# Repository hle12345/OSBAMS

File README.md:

# OSBAMS — Rev.2

**OSBAMS Rev.2 is a standalone lithium-ion battery characterization platform optimized
around the SFSU Agilent 6060B electronic load. It uses an STM32L476RG safety controller,
Raspberry Pi 5 interface, INA228-based measurement, independent voltage verification, and
Keysight reference instrumentation to validate capacity, energy, DCIR, thermal behavior, and
battery health metrics of compatible lithium-ion battery packs within the verified hardware envelope.**

Supported: lithium-ion packs, approximately 30–42 V (10S-class; Ninebot/Segway, Shenzhen Elite), XT60 (connector type does not determine test capability — the validated power path does).
Status: **2.0.0-dev1 — host- and simulator-tested; no physical validation has been run**
(nothing is BENCH_TESTED or HARDWARE_VALIDATED).

## The one rule
`allowed current = min(battery profile, OSBAMS hardware limit, 6060B current limit, 300 W / battery voltage)`
at the conservative (never-sagging) pack voltage. 42 V → **7.14 A**; 36 V → **8.33 A**. The 60 A rating never
overrides 300 W. Operating ceiling: ≤ 44 V and ≤ 10 A until the power path is physically validated.

## The Rev.2 stack (`docs/rev2/SFSU_EQUIPMENT_MATRIX.md`)
Agilent/Keysight **6060B** (primary and only external load) · Keysight **EDU34450A** (reference measurement) ·
**Raspberry Pi 5 + 10.1" touchscreen** (UI, database, passport, reports) · **STM32L476RG** (safety controller) ·
**power path** (battery → XT60 → fuse → disconnect → relay → shunt → 6060B) · Keysight **EDUX1052G** (validation-only observation).

## Test orchestrator and dashboard
`services/test_orchestrator.py`: Capacity (`PROFILE → OCV screen → hardware safety check → capability calculation → READY → CC discharge → cutoff → load OFF verified → recovery → results`) and a separate DCIR current-step test. The dashboard shows the live permitted-current breakdown and drives a *manual* 6060B (operator sets/enables the load; OSBAMS verifies from measurements). Hard invariant: commanded current × conservative pack voltage ≤ 300 W; sag never raises current.

## Open at multiple levels
**Current status of the calibration / validation / AI work (under development)**
- The Rev.2 PCB remains frozen at RC1.2e (release candidate, not bench-validated until first article); the validation/AI work makes no PCB or schematic geometry change.
- Protocol v2 firmware is still under development: only a host-side reference parser, golden vectors and design exist; the STM32 firmware still speaks protocol v1.
- Calibration, measurement-quality and agreement thresholds (and the rule-baseline thresholds) are provisional until real bench/reference-instrument measurements exist.
- The AI/data work is experimental/research-stage; no ML-based battery-health result is production-valid yet, and capacity retention vs rated is not a validated cell-level SOH.

OSBAMS is a platform for assessing unknown and second-life batteries, not just a low-cost cycler: **open hardware** (Rev.2 controller PCB review package), **open firmware and software**, **open battery profiles and test protocols**, **open standardized data** (`docs/rev2/DATASET_SCHEMA.md`, Battery Passport) and **open health models** (`ai/`). Chain: Rev.2 hardware → calibration/validation layer → real battery dataset → explainable AI health assessment. The calibration/validation and AI work is **under development**: thresholds are provisional until reference-instrument validation, Rev.2 remains unbench-validated until first article, AI health estimation is experimental/research-stage, and capacity retention is not a validated cell-level SOH. See `docs/rev2/WORKSTREAMS.md`, `docs/rev2/VALIDATION_AND_CALIBRATION_PLAN.md`, `ai/README.md`.

## Hardware workstreams
Two separate hardware workstreams live in this (private) repo: the **Rev.2 controller PCB** (`Hardware/Rev2_Controller/`, RC1.2e) and the **Pi/display power distribution board plus Pi-power interposer** (`OSBAMS_Pi_Display_Power_RevA_RC1/`, `OSBAMS_Pi_Power_Interposer_RevA_RC1/`, generators in `tools/pi_display_power/`; isolated 12 V → 5 V for the Pi 5 + display). Neither is bench-validated. See `docs/rev2/PI_POWER_WORKSTREAM.md`.

## Next milestone: first real battery test
`docs/rev2/FIRST_BATTERY_TEST_PROCEDURE.md`, with `CALIBRATION_RECORD_TEMPLATE.md` and `HARDWARE_ACCEPTANCE_RECORD.md`. Software is ahead of hardware; no more features until measurements exist.

## Bench work
`docs/rev2/BENCH_CHECKLIST.md` — the exact physical tests, in order (workflow: `LV_HARDWARE_VALIDATION_PLAN.md`; verification: `INSTRUMENT_CALIBRATION_PLAN.md`). `docs/rev2/6060B_DRIVER_EVIDENCE.md` — remote-control command evidence (nothing VERIFIED yet).

## Controller PCB manufacturing package
`manufacturing/PCBWay_OSBAMS_Rev2_PCBA/` — candidate Gerber/BOM/CPL/PDFs for the KiCad controller PCB, with a design review and checklist. **Not production-ready** (see its README and checklist).

## Layout
- `desktop/` — Python application (`equipment/`, `services/`, `db/`, `gui/`)
- `Firmware/` — STM32 firmware + host C tests
- `docs/rev2/` — architecture, power-path matrix, current-sensing redesign, GPIB checklist, validation plan, baseline
- `legacy/rev1/` — archived Rev.1 code (nothing may import it)
- `tests/`, `tools/` — Python tests; simulator and demo-data tools

## Run the tests
```
pip install pytest numpy scikit-learn
python3 -m pytest tests          # also: pyserial PySide6 pyqtgraph; QT_QPA_PLATFORM=offscreen
make -C Firmware/Tests run
```
Learning Mode demo: `cd desktop && python3 -m services.learning_mode`.
Simulator: `python3 tools/simulate_serial.py --list`.

## 6060B remote control
`6060B_REMOTE_CONTROL = BLOCKED_BY_INTERFACE_CONFIRMATION` until the lab's GPIB
path is confirmed (`docs/rev2/GPIB_INTERFACE_CONFIRMATION.md`). Use `Manual6060B`
or `Simulator6060B` meanwhile.

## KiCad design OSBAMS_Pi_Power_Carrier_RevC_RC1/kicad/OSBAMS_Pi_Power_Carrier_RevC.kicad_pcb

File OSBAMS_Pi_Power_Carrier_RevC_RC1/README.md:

# OSBAMS_Pi_Power_Carrier_RevC — RC1

**RevC is the size-optimised layout of the combined Pi/display power carrier: same schematic, same parts, same BOM, same 10 mm isolation rule as RevB RC1 (kept unchanged as the previous candidate). Layout-only change, 65 × 50 mm. Modeled quantities are listed in `docs/BENCH_REQUIRED.md` (not verified).** RC2 + interposer remain superseded, reference-only designs.

**Status: review candidate for the owner's local KiCad 10 ERC/DRC and Gerber export. No Gerbers are included; not a fabrication authorization.** `OSBAMS_Pi_Power_Carrier_RevB_RC1` (85 × 67.5 mm) and the RC2 reference design are unchanged.

One board replaces the separate Pi/display power PCB, the Pi interposer and the Micro-Fit harness between them:
`120 VAC → XDR-75-12 → 12 V → J_IN → F1 0407008.WR → TVS1 SMBJ15A → RSDW40F-05 (isolated) → F2 0451008.MRL → 5V_PI → Pi header pins 2,4 (+5 V) / 6,9,14,20 (GND)` and `5V_PI → J_DISP → Waveshare 10.1-DSI-TOUCH-A`.
`PI_GND` is isolated from `12V_GND`; the only link is inside U1.

## Mechanical concept
**65 × 50 mm plain rectangle** (RevB: 85 × 67.5 mm, −43 % area), 2 layers, 1.6 mm, 2 oz Cu. The upper 65 × 42 mm **main body lies entirely outside the Pi 5 outline** (beside/above the Pi's header edge); the lower 8 mm strip is the **plug tab** (Pi y −0.5…7.5 mm) over the header and carries the Samtec SSW-120-01-L-D socket and the header-end spacer holes M1/M2. The RSDW40F-05 lies with its long axis along x (secondary pins at the left, near the Pi's +5 V / GND header pins; primary pins at the right). `J_IN` (top right) faces the top edge, `J_DISP` (bottom left) faces the left edge. The carrier is **not above the CPU / Active Cooler**. Four M3 NPTH holes take **M3 × 20 mm enclosure standoffs**: they carry the carrier's weight (the socket carries none) and K1/K2 double as the **180° key posts** (reversed, they land on bare Pi PCB and stop the socket 2.5 mm short of the pins). `Mechanical_placement_drawing.pdf`, `reports/Mechanical_fit_check.txt`.

## Gates
| Gate | State |
|---|---|
| KiCad 10.0.6 ERC / DRC incl. schematic-parity / unconnected / footprint errors | **0 / 0 / 0 / 0** (`reports/*_kicad10.rpt`); owner re-runs locally |
| Isolation: ≥ 10 mm PRIMARY↔ISOLATED custom rule, negative control, 11 mm copper-free lane, no copper crossing, NPTH holes, no shield | **PASS** (`reports/Isolation_check.txt`, `docs/Isolation_report.md`) |
| Pin map: power only on Pi pins 2, 4 (+5 V) and 6, 9, 14, 20 (GND); 34 pins no-connect; polarity; module pins vs the Mean Well drawing | **PASS** — 97 checks (`reports/Connectivity_pinmap_check.txt`) |
| Mechanical fit (plan view vs Pi 5 drawing, key, heights) | **PASS on paper**; physical fit at first article (no STEP models available) |
| Voltage budget recomputed from scratch | worst case **4.955 V** at the Pi pins with 5 A + 1.0 A display (RevB: 4.962 V, RC2: 4.829 V) — `docs/Voltage_drop_report.md` |
| Bench-required quantities (SSW contact resistance, module joint resistance, real Waveshare current, mechanical fit, reversed-fit key test, no-load maximum 5.234 V) | **BENCH_REQUIRED** — `docs/BENCH_REQUIRED.md` |
| First article | **OPEN (by design)** — `docs/First_article_checklist.md` |
| Gerbers / PCBWay CAM / CPL orientation | **OWNER** |

## Contents
`kicad/` project (`.kicad_pro/.kicad_sch/.kicad_pcb`), libraries `OSBAMS_PiPwr.kicad_sym` + `OSBAMS_PiPwr.pretty`, `fp-lib-table`, `sym-lib-table`, `.kicad_dru` (isolation rule) · `bom/` (incl. mechanical hardware and off-board harness lines) · `cpl/` · `docs/` (this README's references, assembly drawings top/bottom, mechanical placement drawing, voltage-drop report, isolation report, first-article checklist, parts and sources, changes vs RevB, trim calibration, assembly notes) · `reports/`.
Regenerate: `CARRIER_REV=C REL=RC1 python3 tools/pi_display_power/build_carrier_k10.py <out_root>` (needs the `kc10_pi` KiCad 10 container wrapper).

## Open items (none changes the PCB geometry unless noted)
First-article measurements (trim calibration, contact resistances, loaded voltage at the Pi pins and J_DISP, temperatures, Pi + display, throttling, isolation resistance, reversed-fit test); Waveshare maximum current (unpublished); 43030-0038 current rating with 18 AWG; SSW hole 1.0 mm / pad 1.7 mm vs Samtec's recommended hole; Molex 43045 library footprints vs the Molex drawing; manufacturer data that was relayed by the owner (Waveshare, Samtec, SMBJ15A row) is marked user-relayed.

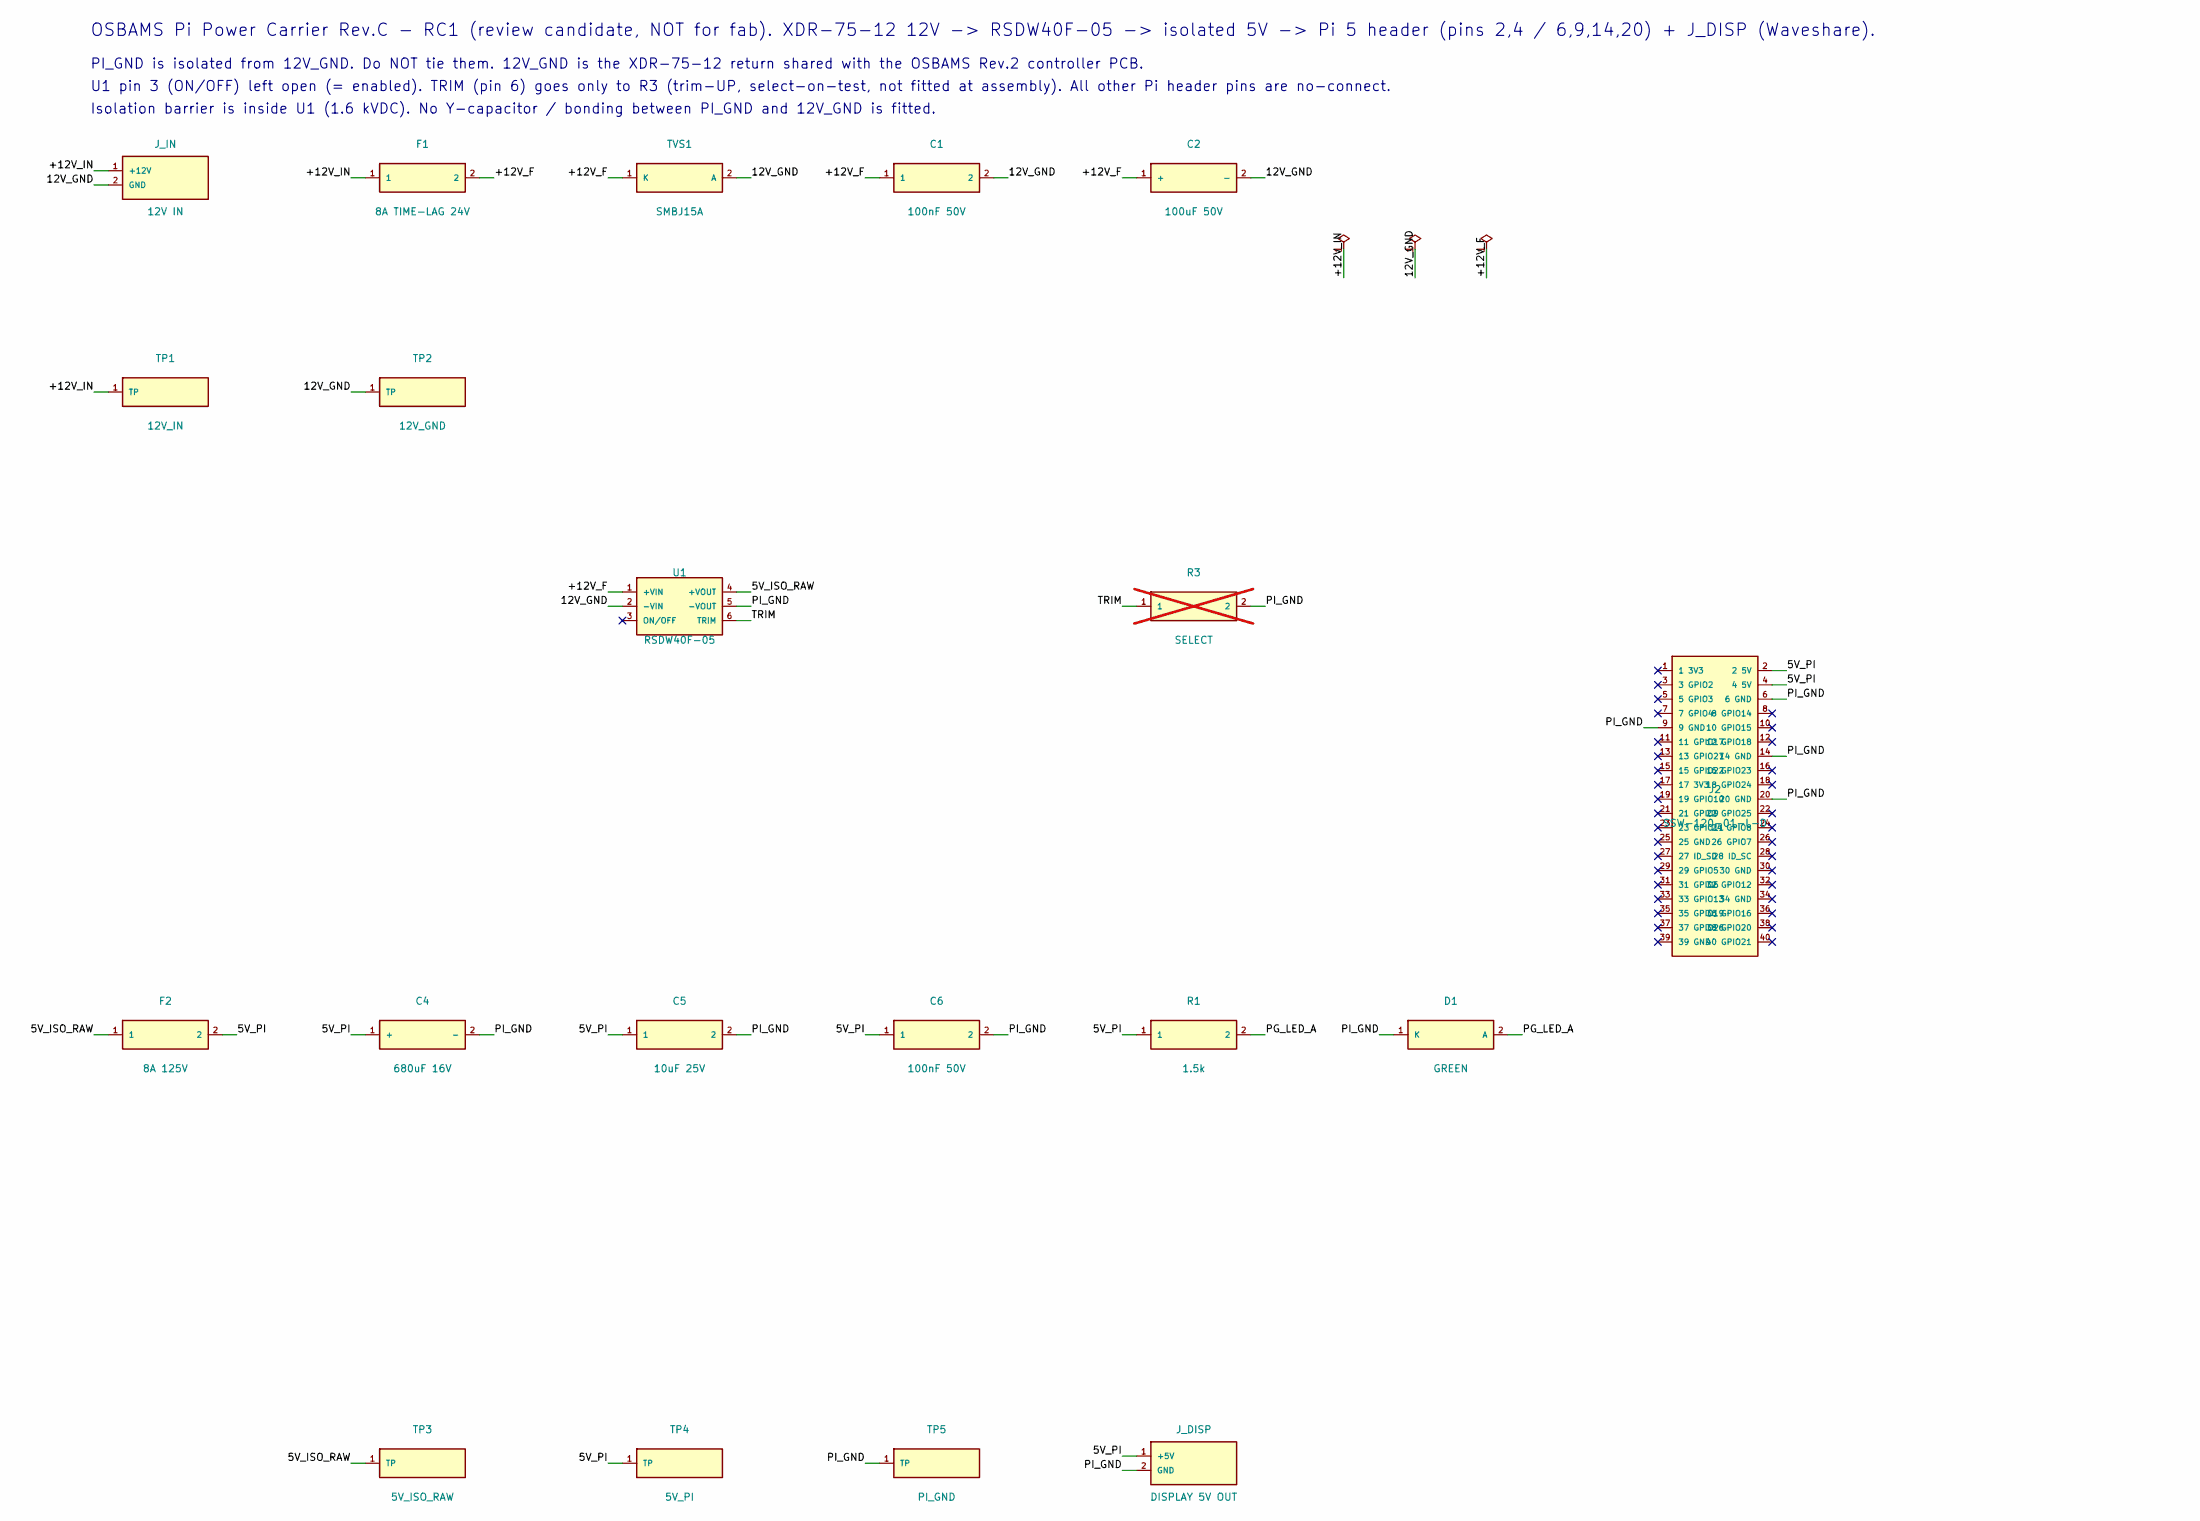
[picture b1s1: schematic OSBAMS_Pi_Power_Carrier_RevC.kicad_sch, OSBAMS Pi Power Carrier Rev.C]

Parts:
C1, C6: 100nF 50V; C_0603_1608Metric; MPN GRM188R71H104KA93D
C2: 100uF 50V; CP_Radial_D8.0mm_P3.50mm; MPN EEU-FM1H101
C4: 680uF 16V; CP_Radial_D10.0mm_P5.00mm; MPN EEU-FR1C681
C5: 10uF 25V; C_0805_2012Metric; MPN GRM21BR61E106KA73L
D1: GREEN; LED_0603_1608Metric; MPN 150060GS75000
F1: 8A TIME-LAG 24V; Fuse_1206_Littelfuse407; MPN 0407008.WR
F2: 8A 125V; Fuse_Littelfuse-NANO2-451_453; MPN 0451008.MRL
J2: SSW-120-01-L-D; SSW-120-01-L-D_RPi_TopView; MPN SSW-120-01-L-D
J_DISP: DISPLAY 5V OUT; Molex_Micro-Fit_3.0_43045-0200_2x01_P3.00mm_Horizontal; MPN 430450200
J_IN: 12V IN; Molex_Micro-Fit_3.0_43045-0200_2x01_P3.00mm_Horizontal; MPN 430450200
R1: 1.5k; R_0603_1608Metric; MPN RC0603FR-071K5L
R3: SELECT; R_0603_1608Metric; MPN RC0603FR-0771K5L (nominal) / -0761K9L /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; not fitted
TP1: 12V_IN; TestPoint_Pad_D1.5mm; MPN 5015
TP2: 12V_GND; TestPoint_Pad_D1.5mm; MPN 5015
TP3: 5V_ISO_RAW; TestPoint_Pad_D1.5mm; MPN 5015
TP4: 5V_PI; TestPoint_Pad_D1.5mm; MPN 5015
TP5: PI_GND; TestPoint_Pad_D1.5mm; MPN 5015
TVS1: SMBJ15A; D_SMB; MPN SMBJ15A
U1: RSDW40F-05; RSDW40F-05_MeanWell_2x1in; MPN RSDW40F-05

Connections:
/5V_ISO_RAW: F2.1, TP3.1, U1.4 (+VOUT)
/5V_PI: C4.1 (+), C5.1, C6.1, F2.2, J2.2 (2 5V), J2.4 (4 5V), J_DISP.1 (+5V), R1.1, TP4.1
/12V_GND: C1.2, C2.2 (-), J_IN.2 (GND), TP2.1, TVS1.2 (A), U1.2 (-VIN)
/+12V_F: C1.1, C2.1 (+), F1.2, TVS1.1 (K), U1.1 (+VIN)
/+12V_IN: F1.1, J_IN.1 (+12V), TP1.1
/PG_LED_A: D1.2 (A), R1.2
/PI_GND: C4.2 (-), C5.2, C6.2, D1.1 (K), J2.6 (6 GND), J2.9 (9 GND), J2.14 (14 GND), J2.20 (20 GND), J_DISP.2 (GND), R3.2, TP5.1, U1.5 (-VOUT)
/TRIM: R3.1, U1.6 (TRIM)

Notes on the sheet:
OSBAMS Pi Power Carrier Rev.C - RC1 (review candidate, NOT for fab). XDR-75-12 12V -> RSDW40F-05 -> isolated 5V -> Pi 5 header (pins 2,4 / 6,9,14,20) + J_DISP (Waveshare).
PI_GND is isolated from 12V_GND. Do NOT tie them. 12V_GND is the XDR-75-12 return shared with the OSBAMS Rev.2 controller PCB.
U1 pin 3 (ON/OFF) left open (= enabled). TRIM (pin 6) goes only to R3 (trim-UP, select-on-test, not fitted at assembly). All other Pi header pins are no-connect.
Isolation barrier is inside U1 (1.6 kVDC). No Y-capacitor / bonding between PI_GND and 12V_GND is fitted.

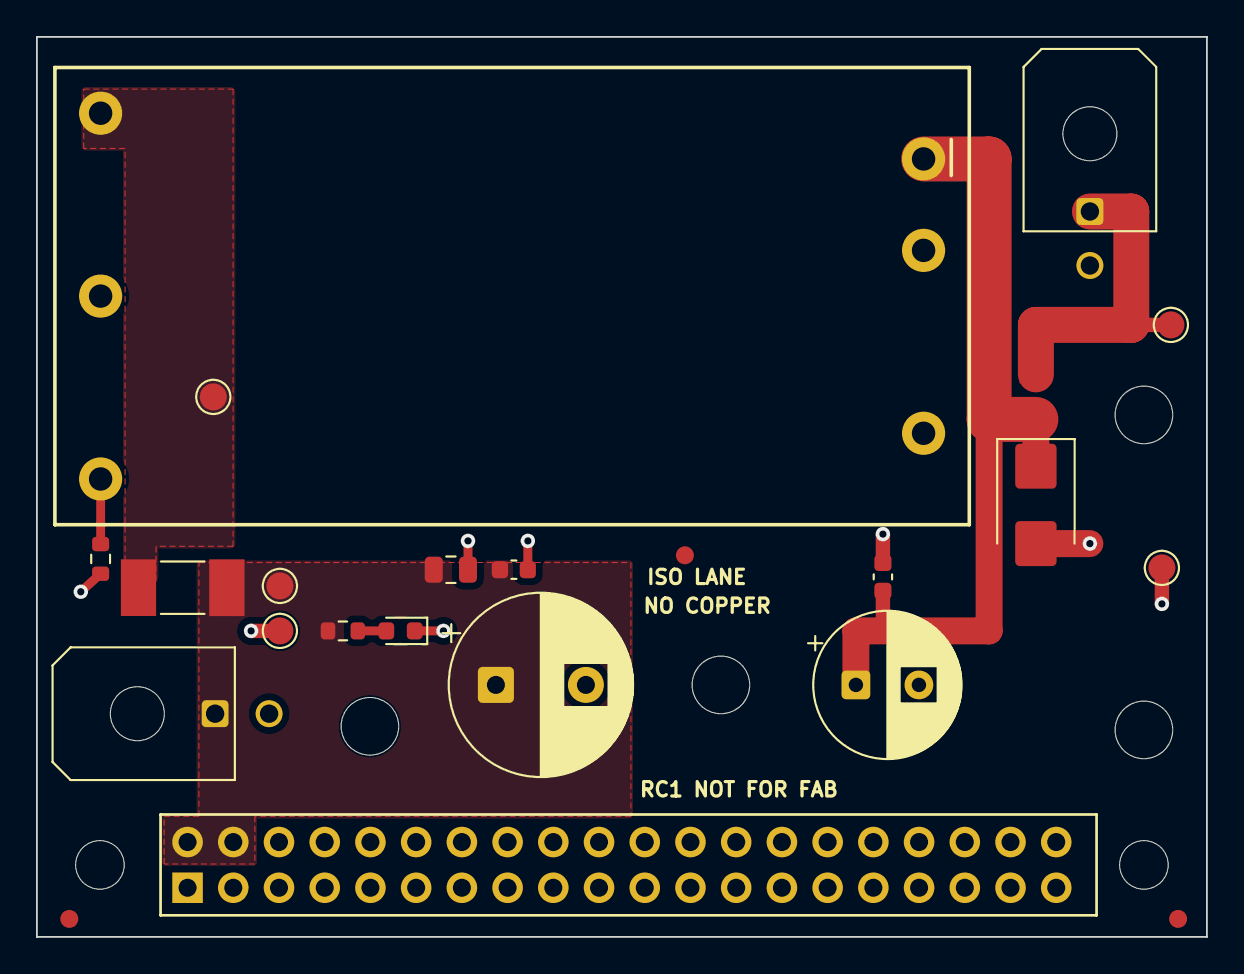
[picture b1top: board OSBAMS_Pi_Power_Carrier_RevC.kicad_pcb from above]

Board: 2 copper layers, 65.0 x 50.0 mm, 29 parts (0 on the bottom side), 8 nets.

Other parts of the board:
FID1, FID2, FID3: Fiducial_1mm_Mask2mm
K1, K2: M3 standoff; MountingHole_3.2mm_M3_Standoff
M1, M2: M2.5 to Pi; MountingHole_2.7mm_M2.5
S3, S4: M3 standoff; MountingHole_3.2mm_M3_Standoff

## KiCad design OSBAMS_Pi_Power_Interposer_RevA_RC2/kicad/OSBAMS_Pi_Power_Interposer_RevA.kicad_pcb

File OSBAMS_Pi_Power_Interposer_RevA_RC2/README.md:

# OSBAMS_Pi_Power_Interposer_RevA — RC2

> **SUPERSEDED / REFERENCE-ONLY by `OSBAMS_Pi_Power_Carrier_RevB_RC1/`** (combined board: worst-case Pi-pin voltage 4.962 V vs 4.829 V here). Kept unchanged as the previous reference design; do not build from it unless RevB is abandoned. PCB geometry is not altered by this note.

Keyed Pi-end interposer for the isolated 5 V supply: Molex Micro-Fit 430450400 (J1) → Samtec **SSW-120-01-L-D** 2 × 20 socket (J2, mounted from the underside) → Raspberry Pi 5 header. **No Gerbers are included; not a fabrication authorization.**

- +5 V on Pi pins **2 and 4**; GND on **6, 9, 14, 20**; the other 34 pins unconnected.
- **Key standoffs K1/K2 (M2.5 × 20 mm) are mandatory**: they prevent the 180° fit that would put +5 V on Pi pin 39 (GND) and GPIO26. Spacers at M1/M2: M2.5 × 11 mm.
- KiCad 10.0.6: ERC 0, DRC 0 (incl. schematic parity), 0 unconnected, 0 footprint errors (`reports/*_kicad10.rpt`).
- Evidence and limits: `docs/Mechanical_verification.md` (Pi 5 drawing, HAT+ geometry, stack height, key), `docs/Keying_analysis.md`, `reports/`.
- Closed: exact socket MPN SSW-120-01-L-D (user-relayed); harness = 18 AWG + Molex 43030-0038 (16 AWG does not fit any 43030 terminal). Open: physical reversed-fit test with a real Pi 5 (first article).
- Project libraries: `kicad/OSBAMS_PiPwr.pretty`, `kicad/OSBAMS_PiPwr.kicad_sym`.

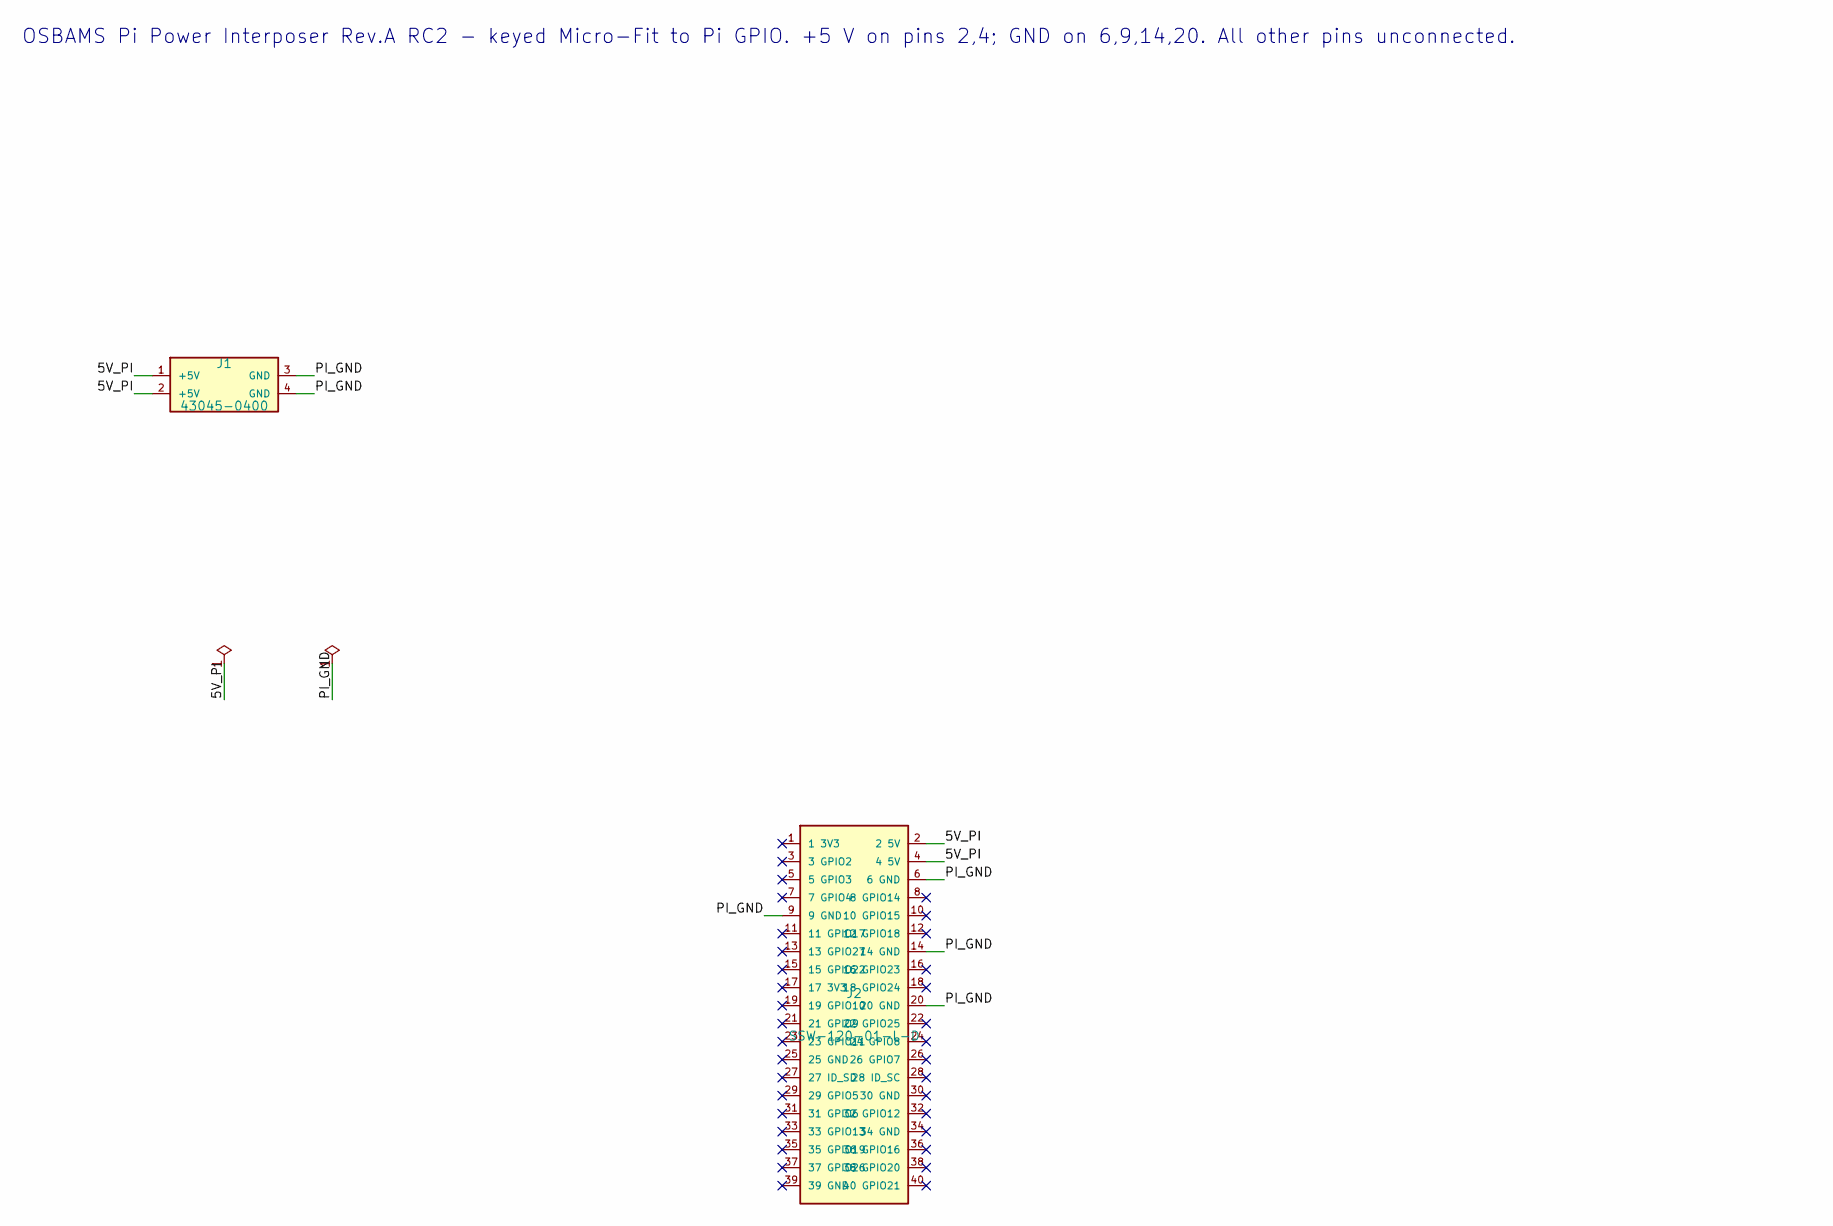
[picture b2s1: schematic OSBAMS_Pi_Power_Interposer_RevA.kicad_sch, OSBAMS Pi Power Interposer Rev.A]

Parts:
J1: 43045-0400; Molex_Micro-Fit_3.0_43045-0400_2x02_P3.00mm_Horizontal; MPN 430450400
J2: SSW-120-01-L-D; SSW-120-01-L-D_RPi_TopView; MPN SSW-120-01-L-D

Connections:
/5V_PI: J1.1 (+5V), J1.2 (+5V), J2.2 (2 5V), J2.4 (4 5V)
/PI_GND: J1.3 (GND), J1.4 (GND), J2.6 (6 GND), J2.9 (9 GND), J2.14 (14 GND), J2.20 (20 GND)

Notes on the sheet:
OSBAMS Pi Power Interposer Rev.A RC2 - keyed Micro-Fit to Pi GPIO. +5 V on pins 2,4; GND on 6,9,14,20. All other pins unconnected.

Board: 2 copper layers, 6 parts (0 on the bottom side), 2 nets, no tracks yet.

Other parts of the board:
K1, K2: KEY M2.5; KeyStandoff_M2.5
M1, M2: M2.5 to Pi; MountingHole_2.7mm_M2.5

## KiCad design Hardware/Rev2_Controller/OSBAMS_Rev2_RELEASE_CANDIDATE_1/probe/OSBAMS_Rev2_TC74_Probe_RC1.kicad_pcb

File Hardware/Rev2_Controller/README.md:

# OSBAMS Rev.2 Controller (new integrated design)

Status: **RELEASE CANDIDATE 1.2 — design package for REVIEW. NOT final, NOT released for fabrication.**
- `OSBAMS_Rev2_RELEASE_CANDIDATE_1/` — KiCad 10 project (schematic, 4-layer PCB, TC74 probe board), BOM/CPL (no Gerbers: export them from the final PCB in KiCad 10), PDFs, ERC/DRC reports, evidence register, supply-chain/DFM/assembly/fab notes, `PCBWAY_RELEASE_CANDIDATE_REPORT.md` (READY FOR REVIEW / BLOCKERS BEFORE PCBWAY ORDER).
- `REV2_CONTROLLER_ARCHITECTURE.md` — architecture (rev D, matches RC1)
- `REV2_CALCULATIONS.md` — generated: `python3 Hardware/Rev2_Controller/calc/rev2_calcs.py` (inputs: `calc/datasheet_inputs.json`, evidence states VERIFIED_LOCAL / USER_RELAYED_MANUFACTURER / UNVERIFIED)
- `REV2_BLOCK_DIAGRAM.png/.svg` (`calc/make_block_diagram.py`), `DATASHEET_VERIFICATION.md` (evidence register)
- `design/` + `build_rc1.py` + `finalize_rc1.py` — generator pipeline (single source of truth `design/rev2_design.py`); `BUILD_ENVIRONMENT.md` explains the KiCad 10 container (`tools/kc10`).
- `reference/` — superseded drafts. Rev.1 KiCad: `legacy/reference/rev1_kicad/` (reference only).
Order: RC1 review → clear every blocker in the RC1 report (manufacturer PDFs, EB21A drawing, local ERC/DRC and Gerber regeneration, stock/lifecycle) → gates in `docs/rev2/pcb/RELEASE_GATES.json` → PCBWay.

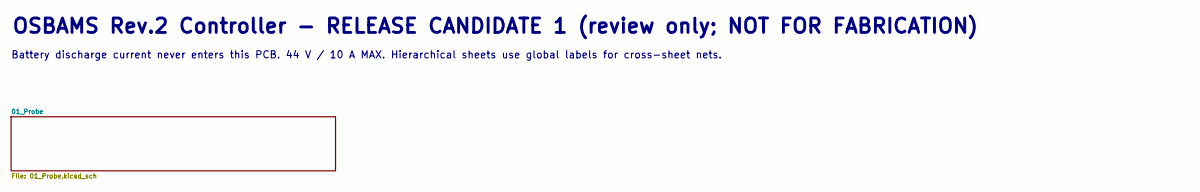
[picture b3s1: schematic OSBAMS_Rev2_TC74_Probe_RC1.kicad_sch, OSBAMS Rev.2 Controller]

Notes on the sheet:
Battery discharge current never enters this PCB. 44 V / 10 A MAX. Hierarchical sheets use global labels for cross-sheet nets.
OSBAMS Rev.2 Controller - RELEASE CANDIDATE 1 (review only; NOT FOR FABRICATION)

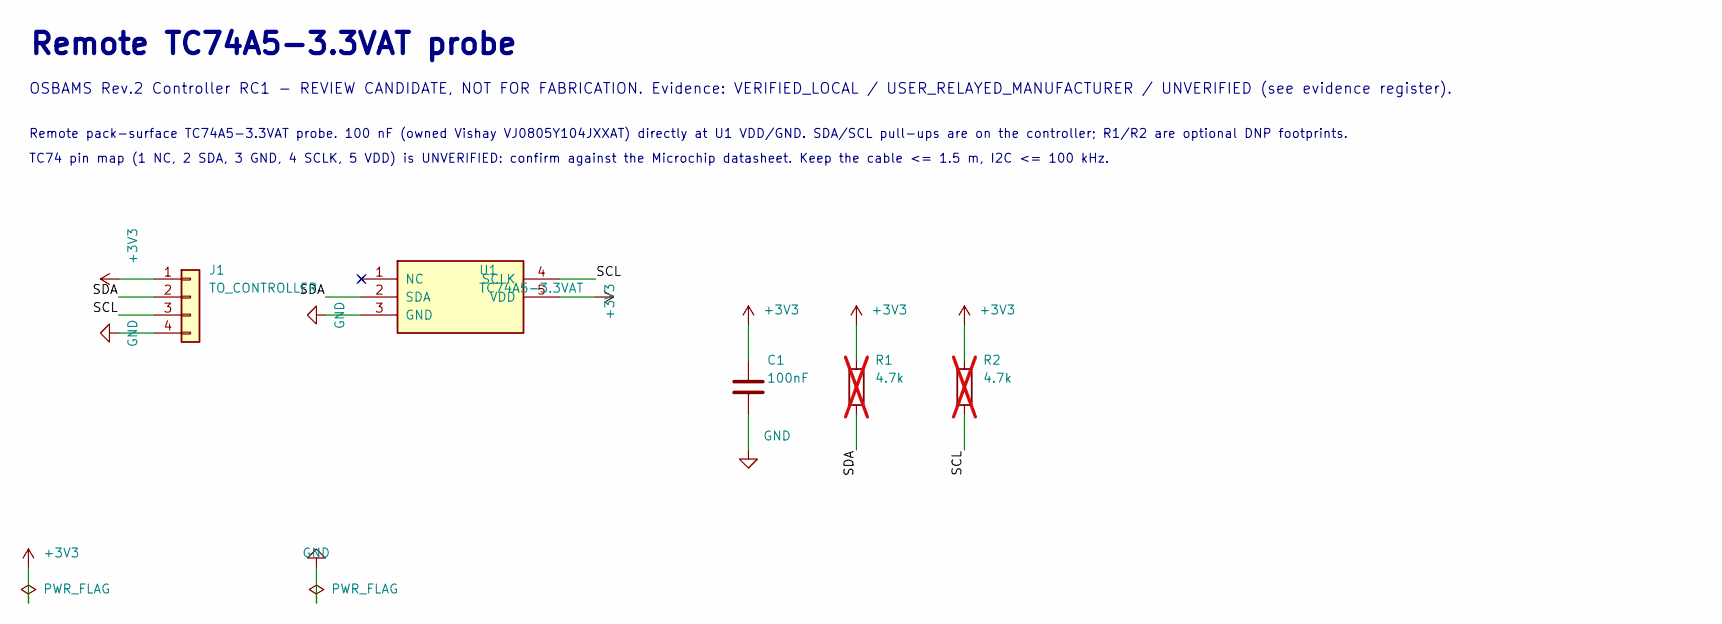
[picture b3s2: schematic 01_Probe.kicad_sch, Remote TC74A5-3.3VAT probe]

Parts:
C1: 100nF; C_0805_2012Metric; MPN VJ0805Y104JXXAT
J1: TO_CONTROLLER; JST_PH_B4B-PH-K_1x04_P2.00mm_Vertical; MPN B4B-PH-K-S
R1, R2: 4.7k; R_0603_1608Metric; MPN CRCW06034K70FKEA; not fitted
U1: TC74A5-3.3VAT; TO-220-5_P3.4x3.7mm_StaggerOdd_Lead3.8mm_Vertical; MPN TC74A5-3.3VAT

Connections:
+3V3: C1.1, J1.1, R1.1, R2.1, U1.5 (VDD)
GND: C1.2, J1.4, U1.3 (GND)
SCL: J1.3, R2.2, U1.4 (SCLK)
SDA: J1.2, R1.2, U1.2 (SDA)

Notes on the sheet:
Remote pack-surface TC74A5-3.3VAT probe. 100 nF (owned Vishay VJ0805Y104JXXAT) directly at U1 VDD/GND. SDA/SCL pull-ups are on the controller; R1/R2 are optional DNP footprints.
TC74 pin map (1 NC, 2 SDA, 3 GND, 4 SCLK, 5 VDD) is UNVERIFIED: confirm against the Microchip datasheet. Keep the cable <= 1.5 m, I2C <= 100 kHz.
OSBAMS Rev.2 Controller RC1 - REVIEW CANDIDATE, NOT FOR FABRICATION. Evidence: VERIFIED_LOCAL / USER_RELAYED_MANUFACTURER / UNVERIFIED (see evidence register).
Remote TC74A5-3.3VAT probe

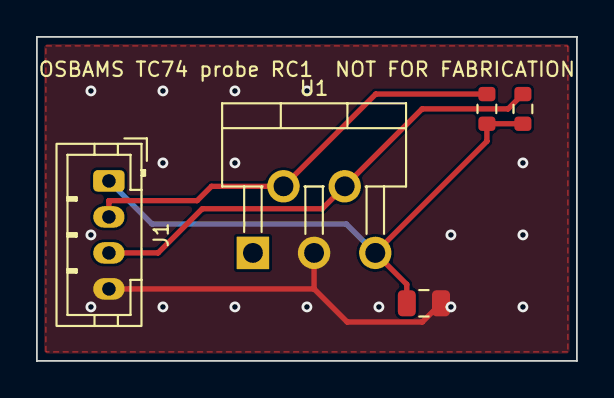
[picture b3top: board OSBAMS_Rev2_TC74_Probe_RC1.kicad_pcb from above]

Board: 2 copper layers, 30.0 x 18.0 mm, 5 parts (0 on the bottom side), 4 nets.

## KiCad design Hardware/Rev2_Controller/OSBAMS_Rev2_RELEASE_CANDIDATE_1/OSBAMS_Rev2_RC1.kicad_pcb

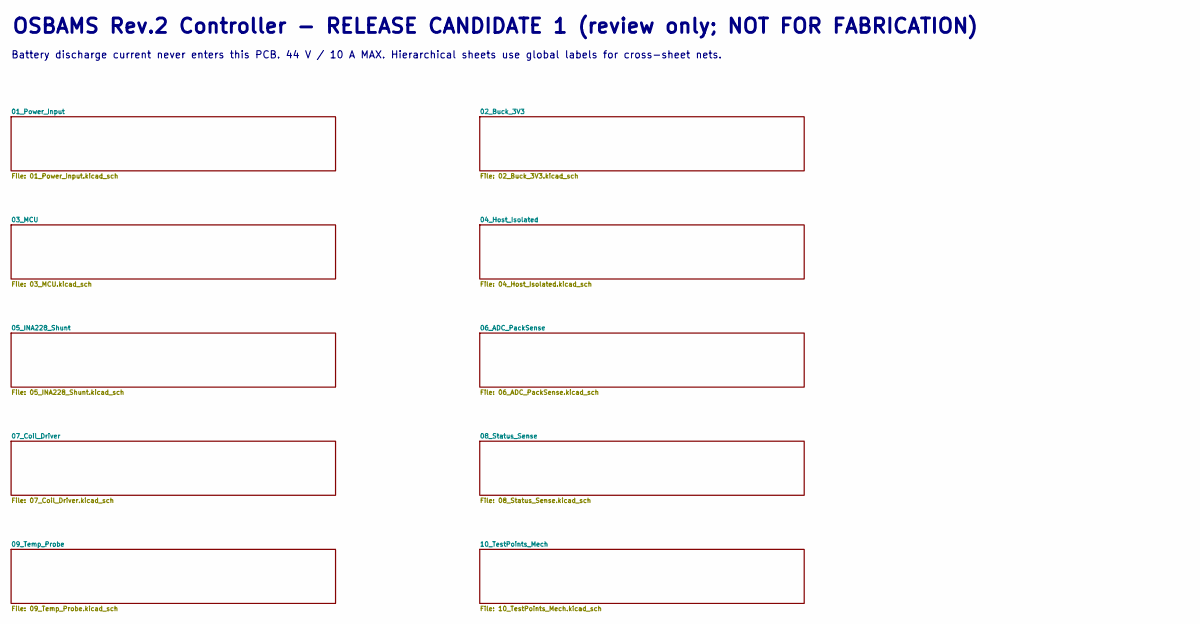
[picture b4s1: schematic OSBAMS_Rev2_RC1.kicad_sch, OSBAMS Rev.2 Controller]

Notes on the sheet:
OSBAMS Rev.2 Controller - RELEASE CANDIDATE 1 (review only; NOT FOR FABRICATION)
Battery discharge current never enters this PCB. 44 V / 10 A MAX. Hierarchical sheets use global labels for cross-sheet nets.

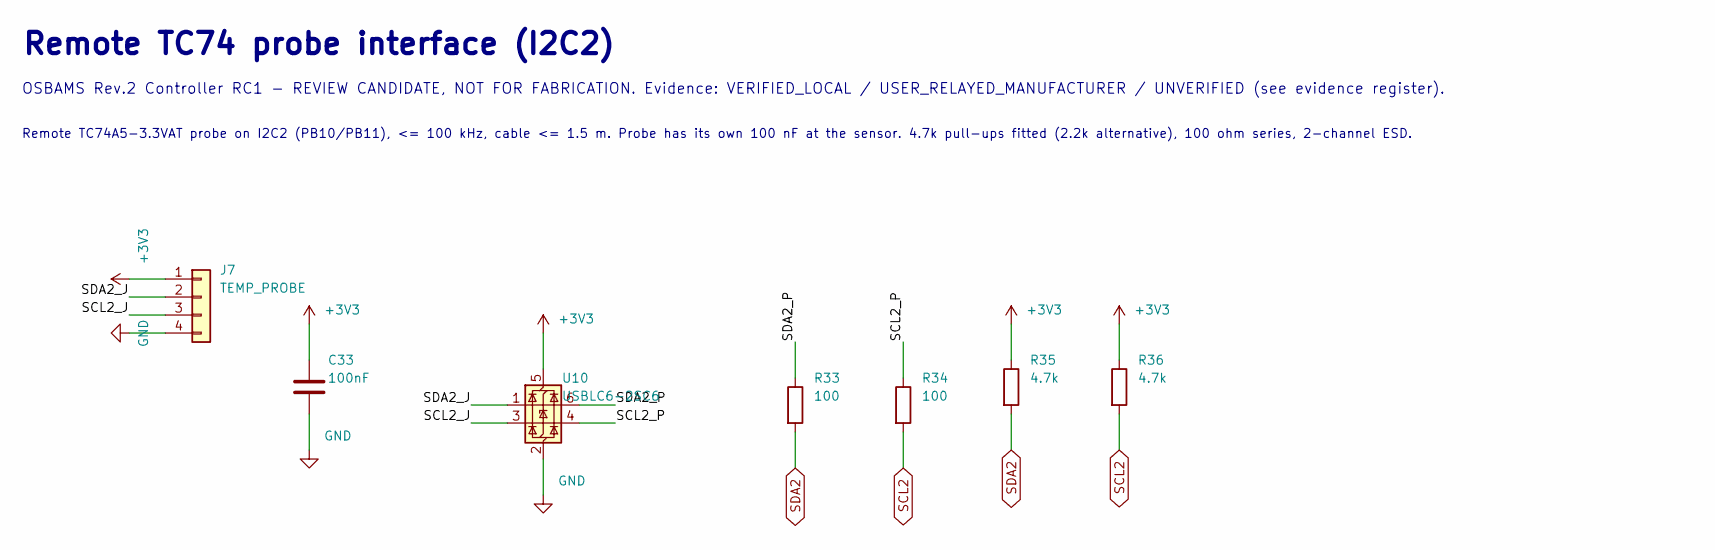
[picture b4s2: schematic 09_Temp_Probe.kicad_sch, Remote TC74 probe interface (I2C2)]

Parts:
C33: 100nF; C_0603_1608Metric; MPN GRM188R71H104KA93D
J7: TEMP_PROBE; JST_PH_B4B-PH-K_1x04_P2.00mm_Vertical; MPN B4B-PH-K-S
R33, R34: 100; R_0603_1608Metric; MPN CRCW0603100RFKEA
R35, R36: 4.7k; R_0603_1608Metric; MPN CRCW06034K70FKEA
U10: USBLC6-2SC6; SOT-23-6; MPN USBLC6-2SC6

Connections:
+3V3: C33.1, J7.1, R35.1, R36.1, U10.5 (VBUS); also elsewhere on the board
/09_Temp_Probe/SCL2_J: J7.3, U10.3 (I/O2)
/09_Temp_Probe/SCL2_P: R34.1, U10.4 (I/O2)
/09_Temp_Probe/SDA2_J: J7.2, U10.1 (I/O1)
/09_Temp_Probe/SDA2_P: R33.1, U10.6 (I/O1)
GND: C33.2, J7.4, U10.2 (GND); also elsewhere on the board
SCL2: R34.2, R36.2; also elsewhere on the board
SDA2: R33.2, R35.2; also elsewhere on the board

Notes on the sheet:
OSBAMS Rev.2 Controller RC1 - REVIEW CANDIDATE, NOT FOR FABRICATION. Evidence: VERIFIED_LOCAL / USER_RELAYED_MANUFACTURER / UNVERIFIED (see evidence register).
Remote TC74 probe interface (I2C2)
Remote TC74A5-3.3VAT probe on I2C2 (PB10/PB11), <= 100 kHz, cable <= 1.5 m. Probe has its own 100 nF at the sensor. 4.7k pull-ups fitted (2.2k alternative), 100 ohm series, 2-channel ESD.

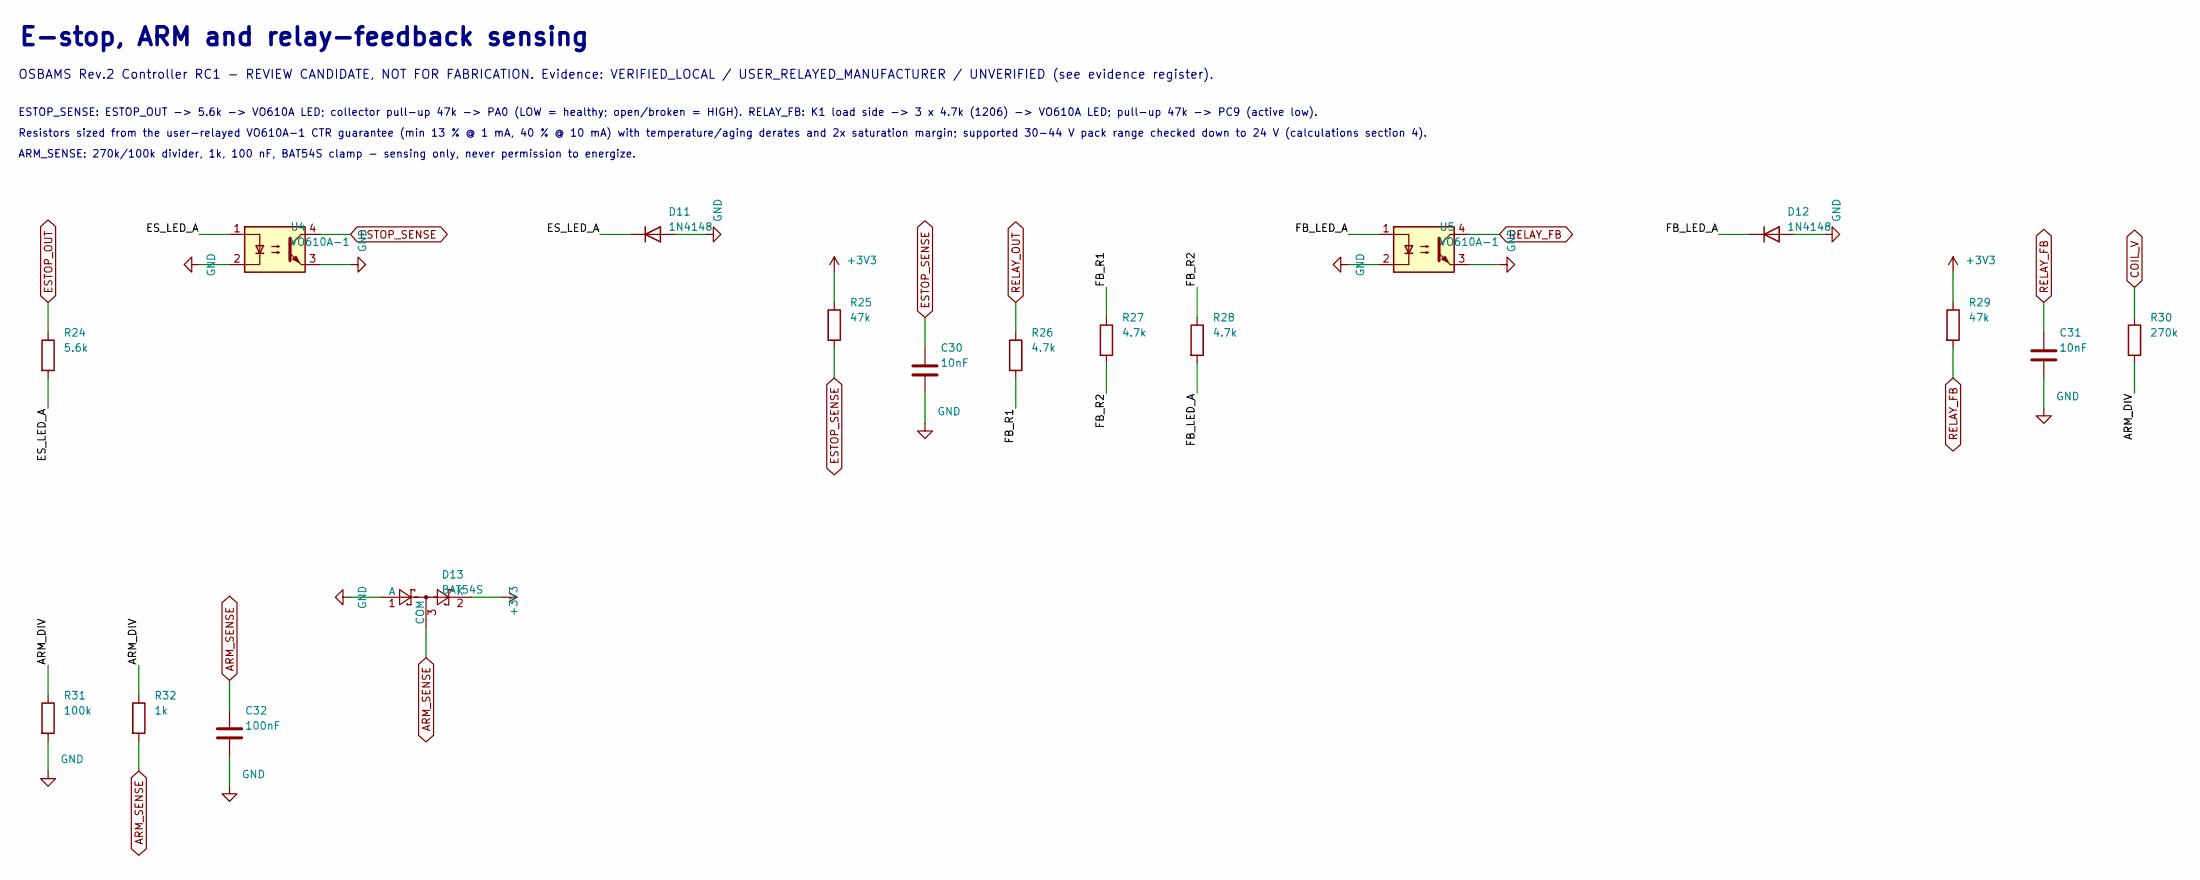
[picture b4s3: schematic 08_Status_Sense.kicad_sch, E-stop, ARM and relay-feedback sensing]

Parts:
C30, C31: 10nF; C_0603_1608Metric; MPN GRM188R71H103KA01D
C32: 100nF; C_0603_1608Metric; MPN GRM188R71H104KA93D
D11, D12: 1N4148; D_DO-35_SOD27_P7.62mm_Horizontal; MPN 1N4148
D13: BAT54S; SOT-23; MPN BAT54S,215
R24: 5.6k; R_0603_1608Metric; MPN CRCW06035K60FKEA
R25, R29: 47k; R_0603_1608Metric; MPN CRCW060347K0FKEA
R26, R27, R28: 4.7k; R_1206_3216Metric; MPN CRCW12064K70FKEA
R30: 270k; R_0603_1608Metric; MPN CRCW0603270KFKEA
R31: 100k; R_0603_1608Metric; MPN CRCW0603100KFKEA
R32: 1k; R_0603_1608Metric; MPN CRCW06031K00FKEA
U4, U5: VO610A-1; DIP-4_W7.62mm; MPN VO610A-1

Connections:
+3V3: D13.2 (K), R25.1, R29.1; also elsewhere on the board
/08_Status_Sense/ARM_DIV: R30.2, R31.1, R32.1
/08_Status_Sense/ES_LED_A: D11.1 (K), R24.2, U4.1
/08_Status_Sense/FB_LED_A: D12.1 (K), R28.2, U5.1
/08_Status_Sense/FB_R1: R26.2, R27.1
/08_Status_Sense/FB_R2: R27.2, R28.1
ARM_SENSE: C32.1, D13.3 (COM), R32.2; also elsewhere on the board
COIL_V: R30.1; also elsewhere on the board
ESTOP_OUT: R24.1; also elsewhere on the board
ESTOP_SENSE: C30.1, R25.2, U4.4; also elsewhere on the board
GND: C30.2, C31.2, C32.2, D11.2 (A), D12.2 (A), D13.1 (A), R31.2, U4.2, U4.3, U5.2, U5.3; also elsewhere on the board
RELAY_FB: C31.1, R29.2, U5.4; also elsewhere on the board
RELAY_OUT: R26.1; also elsewhere on the board

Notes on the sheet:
OSBAMS Rev.2 Controller RC1 - REVIEW CANDIDATE, NOT FOR FABRICATION. Evidence: VERIFIED_LOCAL / USER_RELAYED_MANUFACTURER / UNVERIFIED (see evidence register).
Resistors sized from the user-relayed VO610A-1 CTR guarantee (min 13 % @ 1 mA, 40 % @ 10 mA) with temperature/aging derates and 2x saturation margin; supported 30-44 V pack range checked down to 24 V (calculations section 4).
E-stop, ARM and relay-feedback sensing
ARM_SENSE: 270k/100k divider, 1k, 100 nF, BAT54S clamp - sensing only, never permission to energize.
ESTOP_SENSE: ESTOP_OUT -> 5.6k -> VO610A LED; collector pull-up 47k -> PA0 (LOW = healthy; open/broken = HIGH). RELAY_FB: K1 load side -> 3 x 4.7k (1206) -> VO610A LED; pull-up 47k -> PC9 (active low).

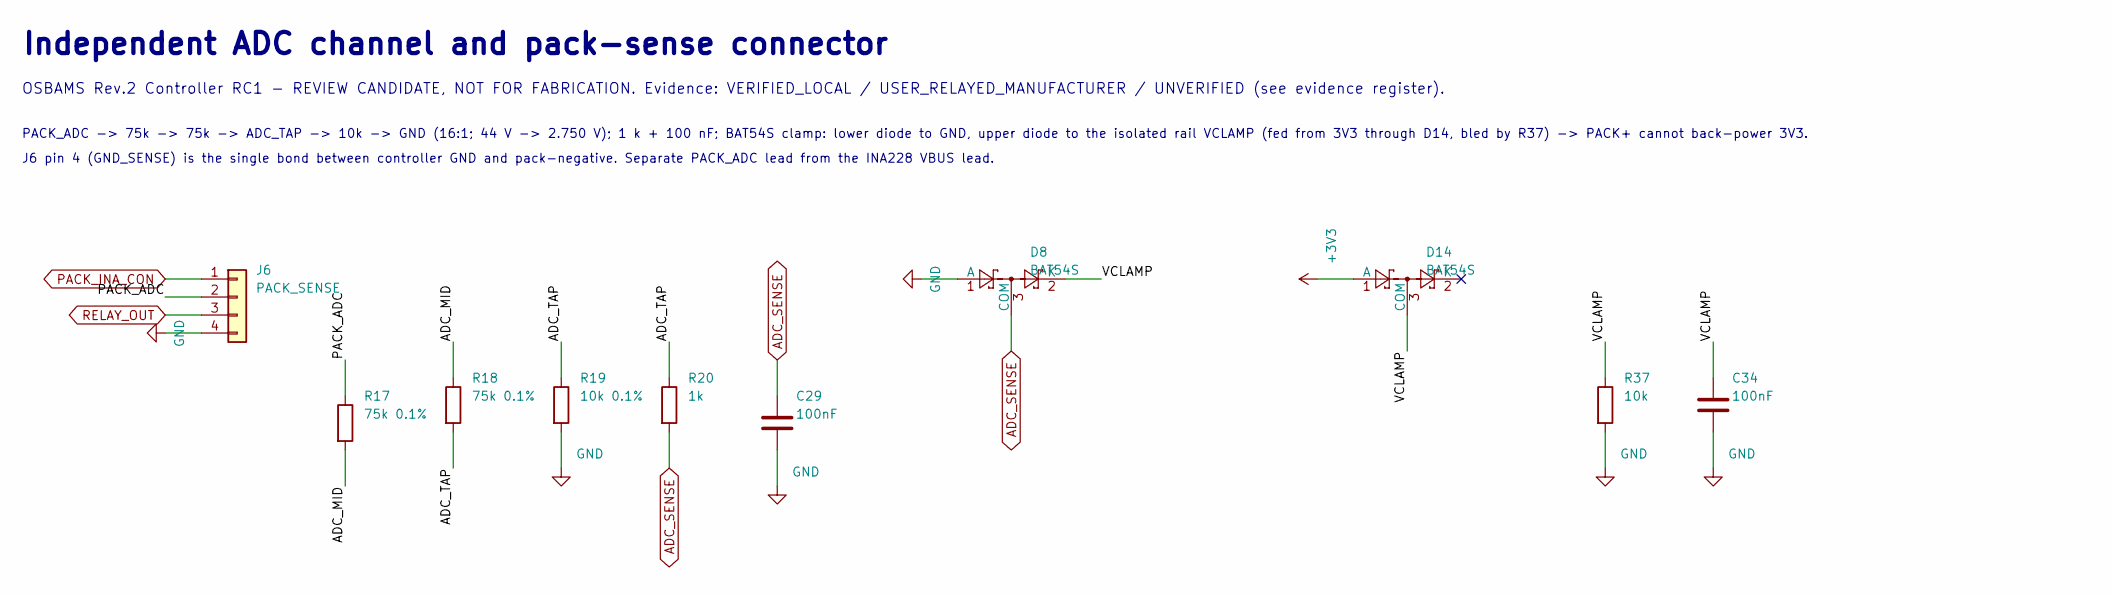
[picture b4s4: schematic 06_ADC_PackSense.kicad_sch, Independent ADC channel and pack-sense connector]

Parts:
C29, C34: 100nF; C_0603_1608Metric; MPN GRM188R71H104KA93D
D8, D14: BAT54S; SOT-23; MPN BAT54S,215
J6: PACK_SENSE; Molex_KK-254_AE-6410-04A_1x04_P2.54mm_Vertical; MPN 22-27-2041
R17, R18: 75k 0.1%; R_0805_2012Metric; MPN TNPW080575K0BEEA
R19: 10k 0.1%; R_0805_2012Metric; MPN TNPW080510K0BEEA
R20: 1k; R_0603_1608Metric; MPN CRCW06031K00FKEA
R37: 10k; R_0603_1608Metric; MPN CRCW060310K0FKEA

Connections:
+3V3: D14.1 (A); also elsewhere on the board
/06_ADC_PackSense/ADC_MID: R17.2, R18.1
/06_ADC_PackSense/ADC_TAP: R18.2, R19.1, R20.1
/06_ADC_PackSense/PACK_ADC: J6.2, R17.1
/06_ADC_PackSense/VCLAMP: C34.1, D8.2 (K), D14.3 (COM), R37.1
ADC_SENSE: C29.1, D8.3 (COM), R20.2; also elsewhere on the board
GND: C29.2, C34.2, D8.1 (A), J6.4, R19.2, R37.2; also elsewhere on the board
PACK_INA_CON: J6.1; also elsewhere on the board
RELAY_OUT: J6.3; also elsewhere on the board

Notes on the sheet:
OSBAMS Rev.2 Controller RC1 - REVIEW CANDIDATE, NOT FOR FABRICATION. Evidence: VERIFIED_LOCAL / USER_RELAYED_MANUFACTURER / UNVERIFIED (see evidence register).
Independent ADC channel and pack-sense connector
J6 pin 4 (GND_SENSE) is the single bond between controller GND and pack-negative. Separate PACK_ADC lead from the INA228 VBUS lead.
PACK_ADC -> 75k -> 75k -> ADC_TAP -> 10k -> GND (16:1; 44 V -> 2.750 V); 1 k + 100 nF; BAT54S clamp: lower diode to GND, upper diode to the isolated rail VCLAMP (fed from 3V3 through D14, bled by R37) -> PACK+ cannot back-power 3V3.
